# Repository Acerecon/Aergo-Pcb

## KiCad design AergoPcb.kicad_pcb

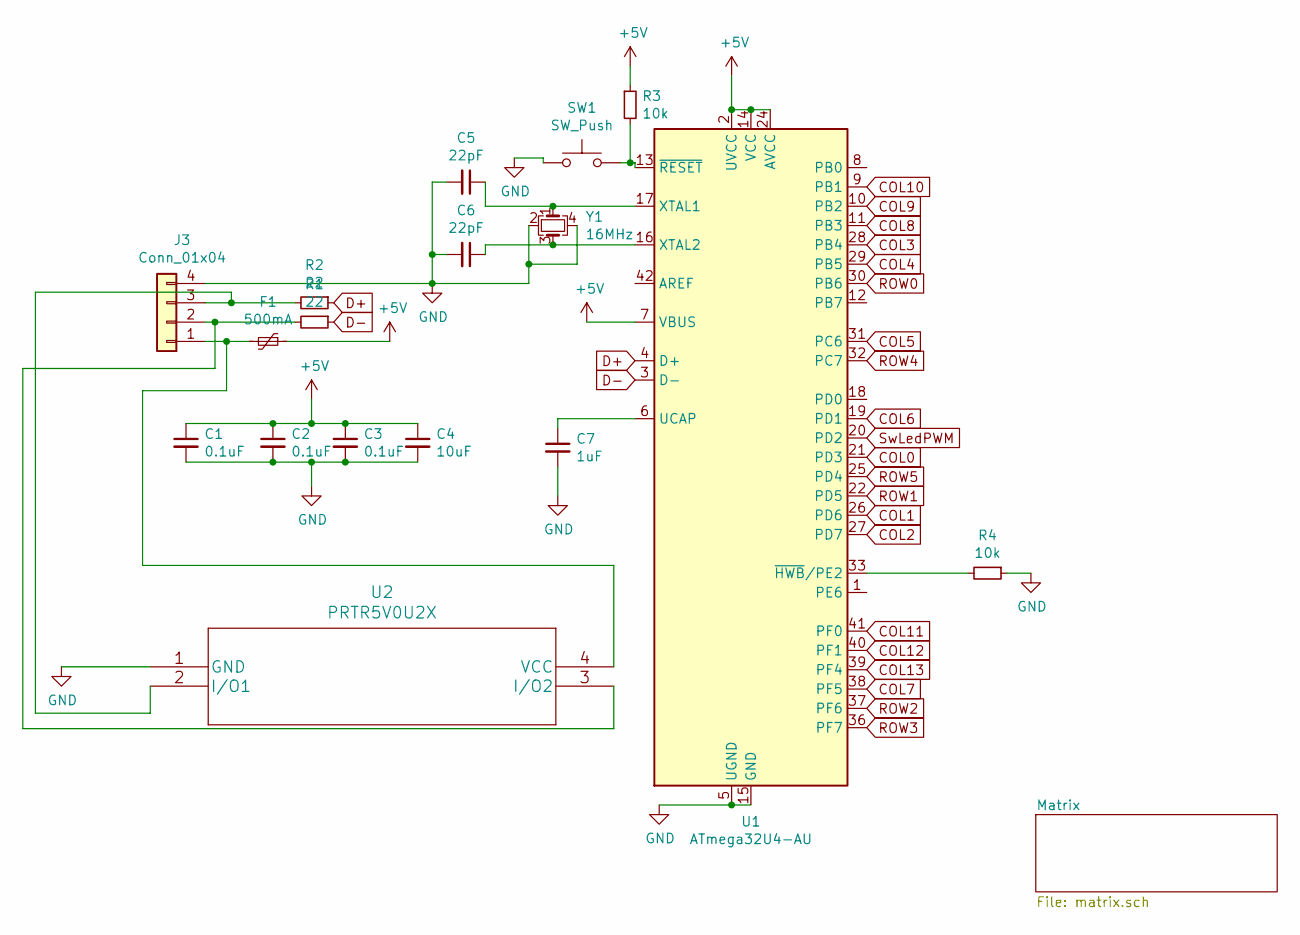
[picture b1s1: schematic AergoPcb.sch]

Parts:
C1, C2, C3: 0.1uF; C_0805_2012Metric
C4: 10uF; C_0805_2012Metric
C5, C6: 22pF; C_0805_2012Metric
C7: 1uF; C_0805_2012Metric
F1: 500mA; Fuse_SMD1206_Reflow
J3: Conn_01x04; JST_SH_SM04B-SRSS-TB_1x04-1MP_P1.00mm_Horizontal
R1, R2: 22; R_0805_2012Metric
R3, R4: 10k; R_0805_2012Metric
SW1: SW_Push; SKQG-1155865
U1: ATmega32U4-AU; TQFP-44_10x10mm_P0.8mm
U2: PRTR5V0U2X; SOT143B
Y1: 16MHz; Crystal_SMD_3225-4Pin_3.2x2.5mm

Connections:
+5V: C1.1, C2.1, C3.1, C4.1, F1.1, R3.1, U1.2 (UVCC), U1.7 (VBUS), U1.14 (VCC), U1.24 (AVCC), U1.34 (VCC), U1.44 (AVCC); also elsewhere on the board
COL0: U1.21 (PD3); also elsewhere on the board
COL1: U1.26 (PD6); also elsewhere on the board
COL2: U1.27 (PD7); also elsewhere on the board
COL3: U1.28 (PB4); also elsewhere on the board
COL4: U1.29 (PB5); also elsewhere on the board
COL5: U1.31 (PC6); also elsewhere on the board
COL6: U1.19 (PD1); also elsewhere on the board
COL7: U1.38 (PF5); also elsewhere on the board
COL8: U1.11 (PB3); also elsewhere on the board
COL9: U1.10 (PB2); also elsewhere on the board
COL10: U1.9 (PB1); also elsewhere on the board
COL11: U1.41 (PF0); also elsewhere on the board
COL12: U1.40 (PF1); also elsewhere on the board
COL13: U1.39 (PF4); also elsewhere on the board
D+: R2.1, U1.4 (D+)
D-: R1.1, U1.3 (D-)
GND: C1.2, C2.2, C3.2, C4.2, C5.2, C6.2, C7.2, J3.4, R4.1, SW1.1, U1.5 (UGND), U1.15 (GND), U1.23 (GND), U1.35 (GND), U1.43 (GND), U2.1 (GND), Y1.2, Y1.4; also elsewhere on the board
unnamed: C5.1, U1.17 (XTAL1), Y1.1
unnamed: C6.1, U1.16 (XTAL2), Y1.3
unnamed: C7.1, U1.6 (UCAP)
unnamed: F1.2, J3.1, U2.4 (VCC)
unnamed: J3.2, R1.2, U2.3 (I/O2)
unnamed: J3.3, R2.2, U2.2 (I/O1)
unnamed: R3.2, SW1.2, U1.13 (~RESET)
unnamed: R4.2, U1.33 (~HWB~/PE2)
ROW0: U1.30 (PB6); also elsewhere on the board
ROW1: U1.22 (PD5); also elsewhere on the board
ROW2: U1.37 (PF6); also elsewhere on the board
ROW3: U1.36 (PF7); also elsewhere on the board
ROW4: U1.32 (PC7); also elsewhere on the board
ROW5: U1.25 (PD4); also elsewhere on the board
SwLedPWM: U1.20 (PD2); also elsewhere on the board

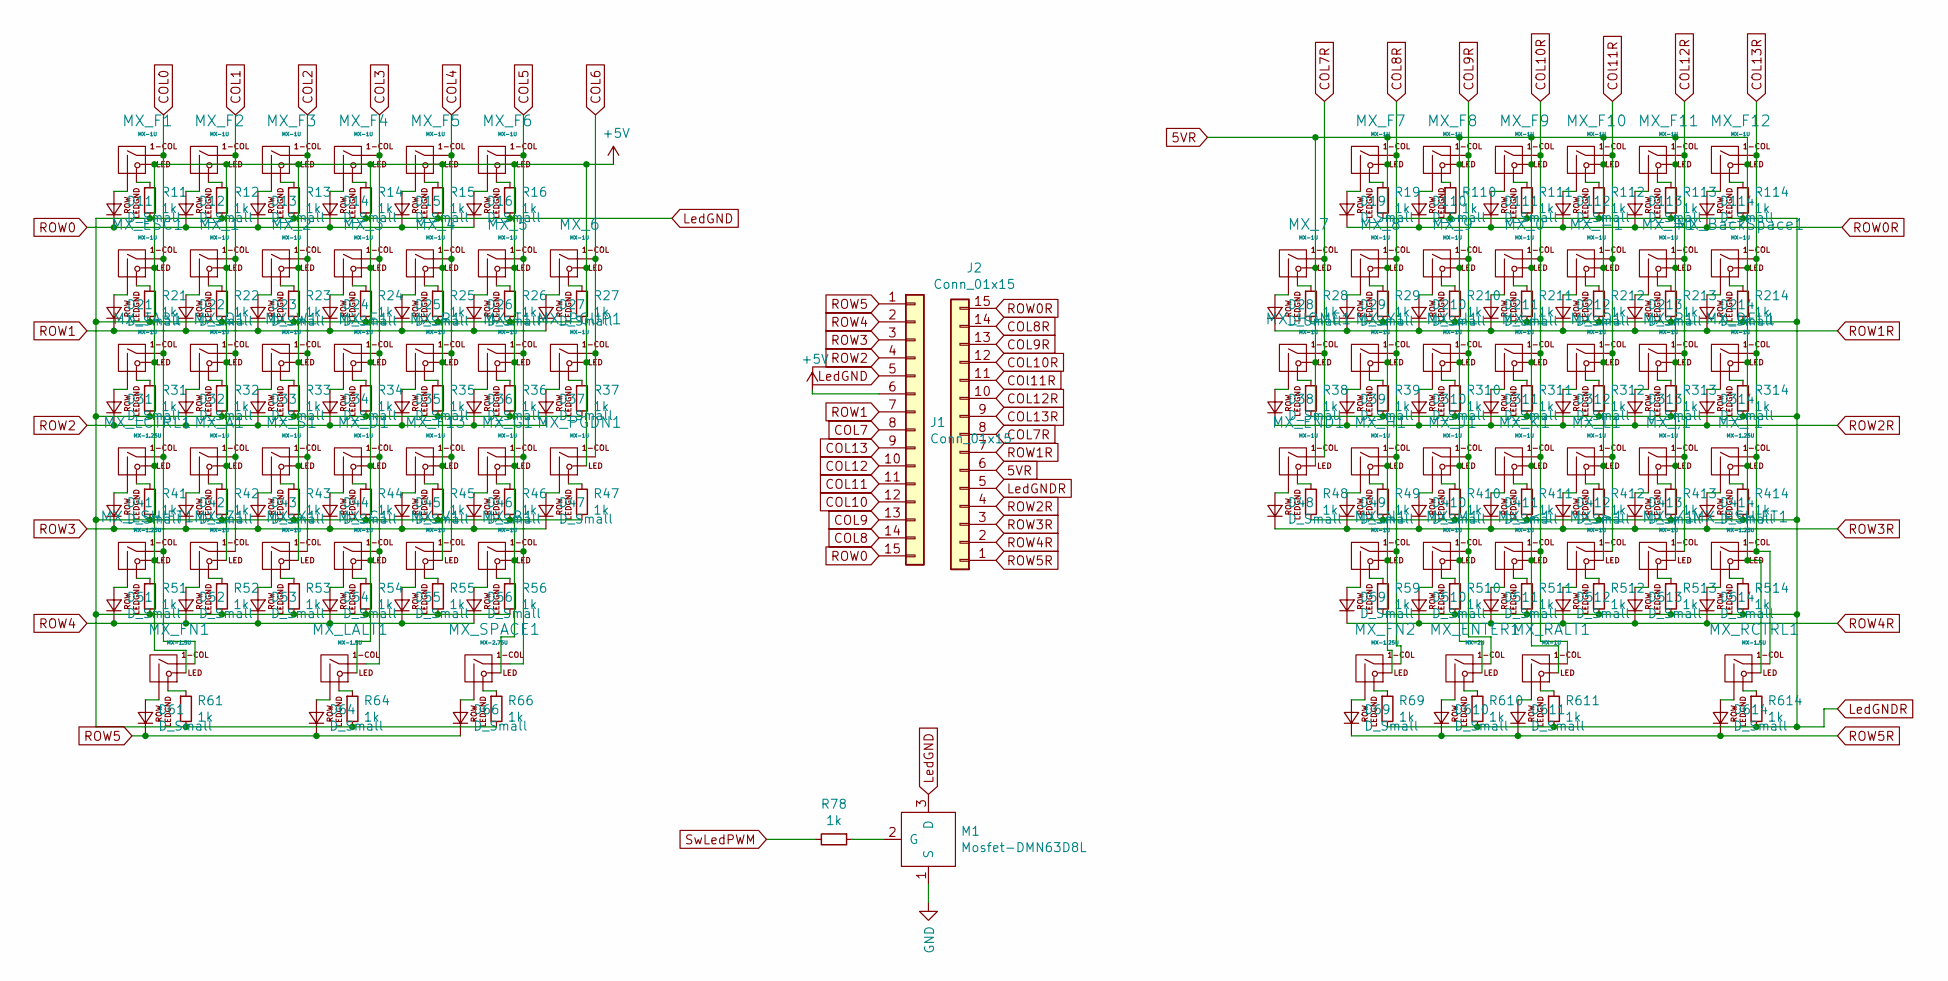
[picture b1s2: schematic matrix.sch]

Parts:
D11, D12, D13, D14, D15, D16, D19, D21, D22, D23, D24, D25, D26, D27, D28, D29, D31, D32, D33, D34, D35, D36, D37, D38, D39, D41, D42, D43, D44, D45, D46, D47, D48, D49, D51, D52, D53, D54, D55, D56, D59, D61, D64, D66, D69, D110, D111, D112, D113, D114, D210, D211, D212, D213, D214, D310, D311, D312, D313, D314, D410, D411, D412, D413, D414, D510, D511, D512, D513, D514, D610, D611, D614: D_Small; D_SOD-123
J1, J2: Conn_01x15; JST_SH_SM15B-SRSS-TB_1x15-1MP_P1.00mm_Horizontal
M1: Mosfet-DMN63D8L
MX_0, MX_1, MX_2, MX_3, MX_4, MX_5, MX_6, MX_7, MX_8, MX_9: MX-1U; MXOnly-1U
MX_'1: MX-1.25U; MXOnly-1.25U
MX_-1: MX-1U; MXOnly-1U
MX_/1: MX-1U; MXOnly-1U
MX_;1: MX-1U; MXOnly-1U
MX_<1: MX-1U; MXOnly-1U
MX_=1: MX-1U; MXOnly-1U
MX_>1: MX-1U; MXOnly-1U
MX_A1: MX-1U; MXOnly-1U
MX_B1: MX-1U; MXOnly-1U
MX_BackSpace1: MX-1U; MXOnly-1U
MX_C1: MX-1U; MXOnly-1U
MX_D1: MX-1U; MXOnly-1U
MX_DEL1: MX-1U; MXOnly-1U
MX_E1: MX-1U; MXOnly-1U
MX_END1: MX-1U; MXOnly-1U
MX_ENTER1: MX-2U; MXOnly-2U-ReversedStabilizers
MX_ESC1: MX-1U; MXOnly-1U
MX_F1, MX_F2, MX_F3, MX_F4, MX_F5, MX_F6, MX_F7, MX_F8, MX_F9, MX_F10, MX_F11, MX_F12, MX_F13: MX-1U; MXOnly-1U
MX_FN1: MX-1.5U; MXOnly-1.5U
MX_FN2: MX-1.25U; MXOnly-1.25U
MX_G1: MX-1U; MXOnly-1U
MX_H1: MX-1U; MXOnly-1U
MX_HOME1: MX-1U; MXOnly-1U
MX_I1: MX-1U; MXOnly-1U
MX_J1: MX-1U; MXOnly-1U
MX_K1: MX-1U; MXOnly-1U
MX_L1: MX-1U; MXOnly-1U
MX_LALT1: MX-1.5U; MXOnly-1.5U
MX_LCTRL1: MX-1.25U; MXOnly-1.25U
MX_LSHIFT1: MX-1.25U; MXOnly-1.25U
MX_M1: MX-1U; MXOnly-1U
MX_N1: MX-1U; MXOnly-1U
MX_O1: MX-1U; MXOnly-1U
MX_P1: MX-1U; MXOnly-1U
MX_PGDN1: MX-1U; MXOnly-1U
MX_PGUP1: MX-1U; MXOnly-1U
MX_Q1: MX-1U; MXOnly-1U
MX_R1: MX-1U; MXOnly-1U
MX_RALT1: MX-1U; MXOnly-1U
MX_RCTRL1: MX-1.5U; MXOnly-1.5U
MX_RSHIFT1: MX-1.25U; MXOnly-1.25U
MX_S1: MX-1U; MXOnly-1U
MX_SPACE1: MX-2.75U; MXOnly-2.75U-ReversedStabilizers
MX_T1: MX-1U; MXOnly-1U
MX_TAB1: MX-1U; MXOnly-1U
MX_U1: MX-1U; MXOnly-1U
MX_V1: MX-1U; MXOnly-1U
MX_W1: MX-1U; MXOnly-1U
MX_X1: MX-1U; MXOnly-1U
MX_Y1: MX-1U; MXOnly-1U
MX_Z1: MX-1U; MXOnly-1U
R11, R12, R13, R14, R15, R16, R19, R21, R22, R23, R24, R25, R26, R27, R28, R29, R31, R32, R33, R34, R35, R36, R37, R38, R39, R41, R42, R43, R44, R45, R46, R47, R48, R49, R51, R52, R53, R54, R55, R56, R59, R61, R64, R66, R69, R78, R110, R111, R112, R113, R114, R210, R211, R212, R213, R214, R310, R311, R312, R313, R314, R410, R411, R412, R413, R414, R510, R511, R512, R513, R514, R610, R611, R614: 1k; R_0805_2012Metric

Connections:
5VR: J2.6, MX_0.3 (LED), MX_7.3 (LED), MX_8.3 (LED), MX_9.3 (LED), MX_'1.3 (LED), MX_-1.3 (LED), MX_/1.3 (LED), MX_;1.3 (LED), MX_<1.3 (LED), MX_=1.3 (LED), MX_>1.3 (LED), MX_BackSpace1.3 (LED), MX_DEL1.3 (LED), MX_END1.3 (LED), MX_ENTER1.3 (LED), MX_F7.3 (LED), MX_F8.3 (LED), MX_F9.3 (LED), MX_F10.3 (LED), MX_F11.3 (LED), MX_F12.3 (LED), MX_FN2.3 (LED), MX_H1.3 (LED), MX_HOME1.3 (LED), MX_I1.3 (LED), MX_J1.3 (LED), MX_K1.3 (LED), MX_L1.3 (LED), MX_M1.3 (LED), MX_N1.3 (LED), MX_O1.3 (LED), MX_P1.3 (LED), MX_RALT1.3 (LED), MX_RCTRL1.3 (LED), MX_RSHIFT1.3 (LED), MX_U1.3 (LED), MX_Y1.3 (LED)
+5V: J1.6, MX_1.3 (LED), MX_2.3 (LED), MX_3.3 (LED), MX_4.3 (LED), MX_5.3 (LED), MX_6.3 (LED), MX_A1.3 (LED), MX_B1.3 (LED), MX_C1.3 (LED), MX_D1.3 (LED), MX_E1.3 (LED), MX_ESC1.3 (LED), MX_F1.3 (LED), MX_F2.3 (LED), MX_F3.3 (LED), MX_F4.3 (LED), MX_F5.3 (LED), MX_F6.3 (LED), MX_F13.3 (LED), MX_FN1.3 (LED), MX_G1.3 (LED), MX_LALT1.3 (LED), MX_LCTRL1.3 (LED), MX_LSHIFT1.3 (LED), MX_PGDN1.3 (LED), MX_PGUP1.3 (LED), MX_Q1.3 (LED), MX_R1.3 (LED), MX_S1.3 (LED), MX_SPACE1.3 (LED), MX_T1.3 (LED), MX_TAB1.3 (LED), MX_V1.3 (LED), MX_W1.3 (LED), MX_X1.3 (LED), MX_Z1.3 (LED); also elsewhere on the board
COL0: MX_ESC1.1 (COL), MX_F1.1 (COL), MX_FN1.1 (COL), MX_LCTRL1.1 (COL), MX_LSHIFT1.1 (COL), MX_TAB1.1 (COL); also elsewhere on the board
COL1: MX_1.1 (COL), MX_A1.1 (COL), MX_F2.1 (COL), MX_Q1.1 (COL), MX_Z1.1 (COL); also elsewhere on the board
COL2: MX_2.1 (COL), MX_F3.1 (COL), MX_S1.1 (COL), MX_W1.1 (COL), MX_X1.1 (COL); also elsewhere on the board
COL3: MX_3.1 (COL), MX_C1.1 (COL), MX_D1.1 (COL), MX_E1.1 (COL), MX_F4.1 (COL), MX_LALT1.1 (COL); also elsewhere on the board
COL4: MX_4.1 (COL), MX_F5.1 (COL), MX_F13.1 (COL), MX_R1.1 (COL), MX_V1.1 (COL); also elsewhere on the board
COL5: MX_5.1 (COL), MX_B1.1 (COL), MX_F6.1 (COL), MX_G1.1 (COL), MX_SPACE1.1 (COL), MX_T1.1 (COL); also elsewhere on the board
COL6: MX_6.1 (COL), MX_PGDN1.1 (COL), MX_PGUP1.1 (COL); also elsewhere on the board
COL7: J1.8; also elsewhere on the board
COL7R: J2.8, MX_7.1 (COL), MX_END1.1 (COL), MX_HOME1.1 (COL)
COL8: J1.14; also elsewhere on the board
COL8R: J2.14, MX_8.1 (COL), MX_F7.1 (COL), MX_FN2.1 (COL), MX_H1.1 (COL), MX_N1.1 (COL), MX_Y1.1 (COL)
COL9: J1.13; also elsewhere on the board
COL9R: J2.13, MX_9.1 (COL), MX_ENTER1.1 (COL), MX_F8.1 (COL), MX_J1.1 (COL), MX_M1.1 (COL), MX_U1.1 (COL)
COL10: J1.12; also elsewhere on the board
COL10R: J2.12, MX_0.1 (COL), MX_<1.1 (COL), MX_F9.1 (COL), MX_I1.1 (COL), MX_K1.1 (COL), MX_RALT1.1 (COL)
COL11: J1.11; also elsewhere on the board
COL12: J1.10; also elsewhere on the board
COL12R: J2.10, MX_/1.1 (COL), MX_;1.1 (COL), MX_=1.1 (COL), MX_F11.1 (COL), MX_P1.1 (COL)
COL13: J1.9; also elsewhere on the board
COL13R: J2.9, MX_'1.1 (COL), MX_BackSpace1.1 (COL), MX_DEL1.1 (COL), MX_F12.1 (COL), MX_RCTRL1.1 (COL), MX_RSHIFT1.1 (COL)
COl11R: J2.11, MX_-1.1 (COL), MX_>1.1 (COL), MX_F10.1 (COL), MX_L1.1 (COL), MX_O1.1 (COL)
GND: M1.1 (S); also elsewhere on the board
LedGND: J1.5, M1.3 (D), R11.2, R12.2, R13.2, R14.2, R15.2, R16.2, R21.2, R22.2, R23.2, R24.2, R25.2, R26.2, R27.2, R31.2, R32.2, R33.2, R34.2, R35.2, R36.2, R37.2, R41.2, R42.2, R43.2, R44.2, R45.2, R46.2, R47.2, R51.2, R52.2, R53.2, R54.2, R55.2, R56.2, R61.2, R64.2, R66.2
LedGNDR: J2.5, R19.2, R28.2, R29.2, R38.2, R39.2, R48.2, R49.2, R59.2, R69.2, R110.2, R111.2, R112.2, R113.2, R114.2, R210.2, R211.2, R212.2, R213.2, R214.2, R310.2, R311.2, R312.2, R313.2, R314.2, R410.2, R411.2, R412.2, R413.2, R414.2, R510.2, R511.2, R512.2, R513.2, R514.2, R610.2, R611.2, R614.2
unnamed: D11.2 (A), MX_F1.2 (ROW)
unnamed: D12.2 (A), MX_F2.2 (ROW)
unnamed: D13.2 (A), MX_F3.2 (ROW)
unnamed: D14.2 (A), MX_F4.2 (ROW)
unnamed: D15.2 (A), MX_F5.2 (ROW)
unnamed: D16.2 (A), MX_F6.2 (ROW)
unnamed: D19.2 (A), MX_F7.2 (ROW)
unnamed: D21.2 (A), MX_ESC1.2 (ROW)
unnamed: D22.2 (A), MX_1.2 (ROW)
unnamed: D23.2 (A), MX_2.2 (ROW)
unnamed: D24.2 (A), MX_3.2 (ROW)
unnamed: D25.2 (A), MX_4.2 (ROW)
unnamed: D26.2 (A), MX_5.2 (ROW)
unnamed: D27.2 (A), MX_6.2 (ROW)
unnamed: D28.2 (A), MX_7.2 (ROW)
unnamed: D29.2 (A), MX_8.2 (ROW)
unnamed: D31.2 (A), MX_TAB1.2 (ROW)
unnamed: D32.2 (A), MX_Q1.2 (ROW)
unnamed: D33.2 (A), MX_W1.2 (ROW)
unnamed: D34.2 (A), MX_E1.2 (ROW)
unnamed: D35.2 (A), MX_R1.2 (ROW)
unnamed: D36.2 (A), MX_T1.2 (ROW)
unnamed: D37.2 (A), MX_PGUP1.2 (ROW)
unnamed: D38.2 (A), MX_HOME1.2 (ROW)
unnamed: D39.2 (A), MX_Y1.2 (ROW)
unnamed: D41.2 (A), MX_LCTRL1.2 (ROW)
unnamed: D42.2 (A), MX_A1.2 (ROW)
unnamed: D43.2 (A), MX_S1.2 (ROW)
unnamed: D44.2 (A), MX_D1.2 (ROW)
unnamed: D45.2 (A), MX_F13.2 (ROW)
unnamed: D46.2 (A), MX_G1.2 (ROW)
unnamed: D47.2 (A), MX_PGDN1.2 (ROW)
unnamed: D48.2 (A), MX_END1.2 (ROW)
unnamed: D49.2 (A), MX_H1.2 (ROW)
unnamed: D51.2 (A), MX_LSHIFT1.2 (ROW)
unnamed: D52.2 (A), MX_Z1.2 (ROW)
unnamed: D53.2 (A), MX_X1.2 (ROW)
unnamed: D54.2 (A), MX_C1.2 (ROW)
unnamed: D55.2 (A), MX_V1.2 (ROW)
unnamed: D56.2 (A), MX_B1.2 (ROW)
unnamed: D59.2 (A), MX_N1.2 (ROW)
unnamed: D61.2 (A), MX_FN1.2 (ROW)
unnamed: D64.2 (A), MX_LALT1.2 (ROW)
unnamed: D66.2 (A), MX_SPACE1.2 (ROW)
unnamed: D69.2 (A), MX_FN2.2 (ROW)
unnamed: D110.2 (A), MX_F8.2 (ROW)
unnamed: D111.2 (A), MX_F9.2 (ROW)
unnamed: D112.2 (A), MX_F10.2 (ROW)
unnamed: D113.2 (A), MX_F11.2 (ROW)
unnamed: D114.2 (A), MX_F12.2 (ROW)
unnamed: D210.2 (A), MX_9.2 (ROW)
unnamed: D211.2 (A), MX_0.2 (ROW)
unnamed: D212.2 (A), MX_-1.2 (ROW)
unnamed: D213.2 (A), MX_=1.2 (ROW)
unnamed: D214.2 (A), MX_BackSpace1.2 (ROW)
unnamed: D310.2 (A), MX_U1.2 (ROW)
unnamed: D311.2 (A), MX_I1.2 (ROW)
unnamed: D312.2 (A), MX_O1.2 (ROW)
unnamed: D313.2 (A), MX_P1.2 (ROW)
unnamed: D314.2 (A), MX_DEL1.2 (ROW)
unnamed: D410.2 (A), MX_J1.2 (ROW)
unnamed: D411.2 (A), MX_K1.2 (ROW)
unnamed: D412.2 (A), MX_L1.2 (ROW)
unnamed: D413.2 (A), MX_;1.2 (ROW)
unnamed: D414.2 (A), MX_'1.2 (ROW)
unnamed: D510.2 (A), MX_M1.2 (ROW)
unnamed: D511.2 (A), MX_<1.2 (ROW)
unnamed: D512.2 (A), MX_>1.2 (ROW)
unnamed: D513.2 (A), MX_/1.2 (ROW)
unnamed: D514.2 (A), MX_RSHIFT1.2 (ROW)
unnamed: D610.2 (A), MX_ENTER1.2 (ROW)
unnamed: D611.2 (A), MX_RALT1.2 (ROW)
unnamed: D614.2 (A), MX_RCTRL1.2 (ROW)
unnamed: M1.2 (G), R78.1
unnamed: MX_0.4 (LEDGND), R211.1
unnamed: MX_1.4 (LEDGND), R22.1
unnamed: MX_2.4 (LEDGND), R23.1
unnamed: MX_3.4 (LEDGND), R24.1
unnamed: MX_4.4 (LEDGND), R25.1
unnamed: MX_5.4 (LEDGND), R26.1
unnamed: MX_6.4 (LEDGND), R27.1
unnamed: MX_7.4 (LEDGND), R28.1
unnamed: MX_8.4 (LEDGND), R29.1
unnamed: MX_9.4 (LEDGND), R210.1
unnamed: MX_'1.4 (LEDGND), R414.1
unnamed: MX_-1.4 (LEDGND), R212.1
unnamed: MX_/1.4 (LEDGND), R513.1
unnamed: MX_;1.4 (LEDGND), R413.1
unnamed: MX_<1.4 (LEDGND), R511.1
unnamed: MX_=1.4 (LEDGND), R213.1
unnamed: MX_>1.4 (LEDGND), R512.1
unnamed: MX_A1.4 (LEDGND), R42.1
unnamed: MX_B1.4 (LEDGND), R56.1
unnamed: MX_BackSpace1.4 (LEDGND), R214.1
unnamed: MX_C1.4 (LEDGND), R54.1
unnamed: MX_D1.4 (LEDGND), R44.1
unnamed: MX_DEL1.4 (LEDGND), R314.1
unnamed: MX_E1.4 (LEDGND), R34.1
unnamed: MX_END1.4 (LEDGND), R48.1
unnamed: MX_ENTER1.4 (LEDGND), R610.1
unnamed: MX_ESC1.4 (LEDGND), R21.1
unnamed: MX_F1.4 (LEDGND), R11.1
unnamed: MX_F2.4 (LEDGND), R12.1
unnamed: MX_F3.4 (LEDGND), R13.1
unnamed: MX_F4.4 (LEDGND), R14.1
unnamed: MX_F5.4 (LEDGND), R15.1
unnamed: MX_F6.4 (LEDGND), R16.1
unnamed: MX_F7.4 (LEDGND), R19.1
unnamed: MX_F8.4 (LEDGND), R110.1
unnamed: MX_F9.4 (LEDGND), R111.1
unnamed: MX_F10.4 (LEDGND), R112.1
unnamed: MX_F11.4 (LEDGND), R113.1
unnamed: MX_F12.4 (LEDGND), R114.1
unnamed: MX_F13.4 (LEDGND), R45.1
unnamed: MX_FN1.4 (LEDGND), R61.1
unnamed: MX_FN2.4 (LEDGND), R69.1
unnamed: MX_G1.4 (LEDGND), R46.1
unnamed: MX_H1.4 (LEDGND), R49.1
unnamed: MX_HOME1.4 (LEDGND), R38.1
unnamed: MX_I1.4 (LEDGND), R311.1
unnamed: MX_J1.4 (LEDGND), R410.1
unnamed: MX_K1.4 (LEDGND), R411.1
unnamed: MX_L1.4 (LEDGND), R412.1
unnamed: MX_LALT1.4 (LEDGND), R64.1
unnamed: MX_LCTRL1.4 (LEDGND), R41.1
unnamed: MX_LSHIFT1.4 (LEDGND), R51.1
unnamed: MX_M1.4 (LEDGND), R510.1
unnamed: MX_N1.4 (LEDGND), R59.1
unnamed: MX_O1.4 (LEDGND), R312.1
unnamed: MX_P1.4 (LEDGND), R313.1
unnamed: MX_PGDN1.4 (LEDGND), R47.1
unnamed: MX_PGUP1.4 (LEDGND), R37.1
unnamed: MX_Q1.4 (LEDGND), R32.1
unnamed: MX_R1.4 (LEDGND), R35.1
unnamed: MX_RALT1.4 (LEDGND), R611.1
unnamed: MX_RCTRL1.4 (LEDGND), R614.1
unnamed: MX_RSHIFT1.4 (LEDGND), R514.1
unnamed: MX_S1.4 (LEDGND), R43.1
unnamed: MX_SPACE1.4 (LEDGND), R66.1
unnamed: MX_T1.4 (LEDGND), R36.1
unnamed: MX_TAB1.4 (LEDGND), R31.1
unnamed: MX_U1.4 (LEDGND), R310.1
unnamed: MX_V1.4 (LEDGND), R55.1
unnamed: MX_W1.4 (LEDGND), R33.1
unnamed: MX_X1.4 (LEDGND), R53.1
unnamed: MX_Y1.4 (LEDGND), R39.1
unnamed: MX_Z1.4 (LEDGND), R52.1
ROW0: D11.1 (K), D12.1 (K), D13.1 (K), D14.1 (K), D15.1 (K), D16.1 (K), J1.15; also elsewhere on the board
ROW0R: D19.1 (K), D110.1 (K), D111.1 (K), D112.1 (K), D113.1 (K), D114.1 (K), J2.15
ROW1: D21.1 (K), D22.1 (K), D23.1 (K), D24.1 (K), D25.1 (K), D26.1 (K), D27.1 (K), J1.7; also elsewhere on the board
ROW1R: D28.1 (K), D29.1 (K), D210.1 (K), D211.1 (K), D212.1 (K), D213.1 (K), D214.1 (K), J2.7
ROW2: D31.1 (K), D32.1 (K), D33.1 (K), D34.1 (K), D35.1 (K), D36.1 (K), D37.1 (K), J1.4; also elsewhere on the board
ROW2R: D38.1 (K), D39.1 (K), D310.1 (K), D311.1 (K), D312.1 (K), D313.1 (K), D314.1 (K), J2.4
ROW3: D41.1 (K), D42.1 (K), D43.1 (K), D44.1 (K), D45.1 (K), D46.1 (K), D47.1 (K), J1.3; also elsewhere on the board
ROW3R: D48.1 (K), D49.1 (K), D410.1 (K), D411.1 (K), D412.1 (K), D413.1 (K), D414.1 (K), J2.3
ROW4: D51.1 (K), D52.1 (K), D53.1 (K), D54.1 (K), D55.1 (K), D56.1 (K), J1.2; also elsewhere on the board
ROW4R: D59.1 (K), D510.1 (K), D511.1 (K), D512.1 (K), D513.1 (K), D514.1 (K), J2.2
ROW5: D61.1 (K), D64.1 (K), D66.1 (K), J1.1; also elsewhere on the board
ROW5R: D69.1 (K), D610.1 (K), D611.1 (K), D614.1 (K), J2.1
SwLedPWM: R78.2; also elsewhere on the board

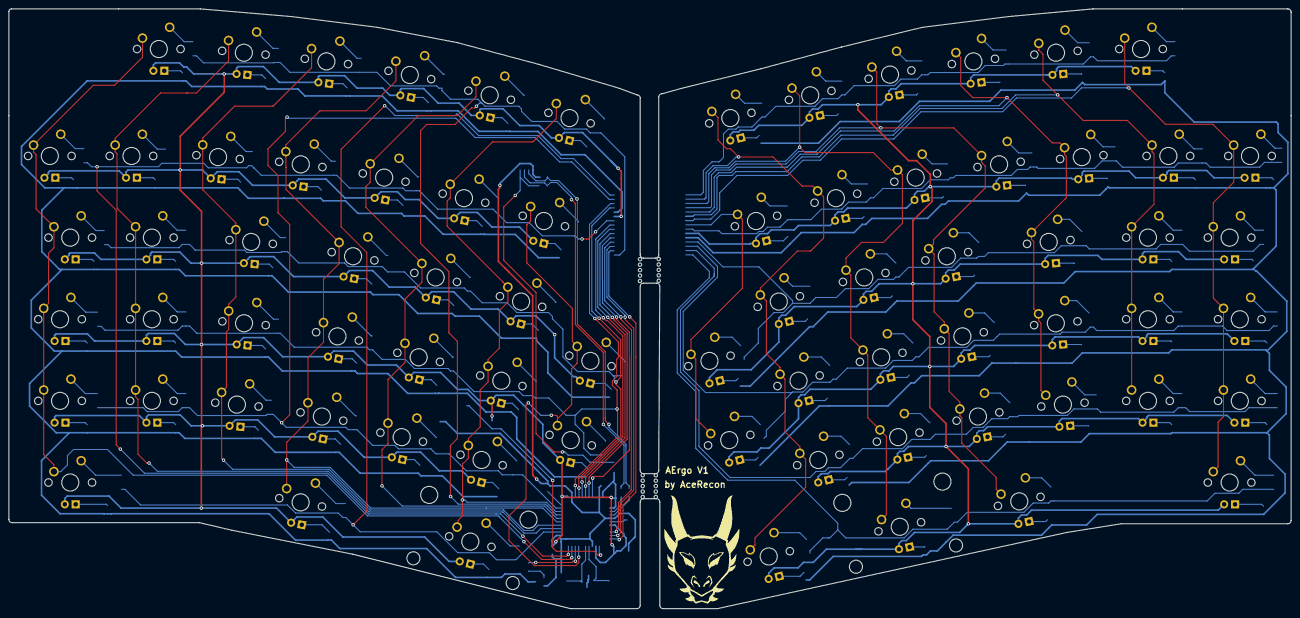
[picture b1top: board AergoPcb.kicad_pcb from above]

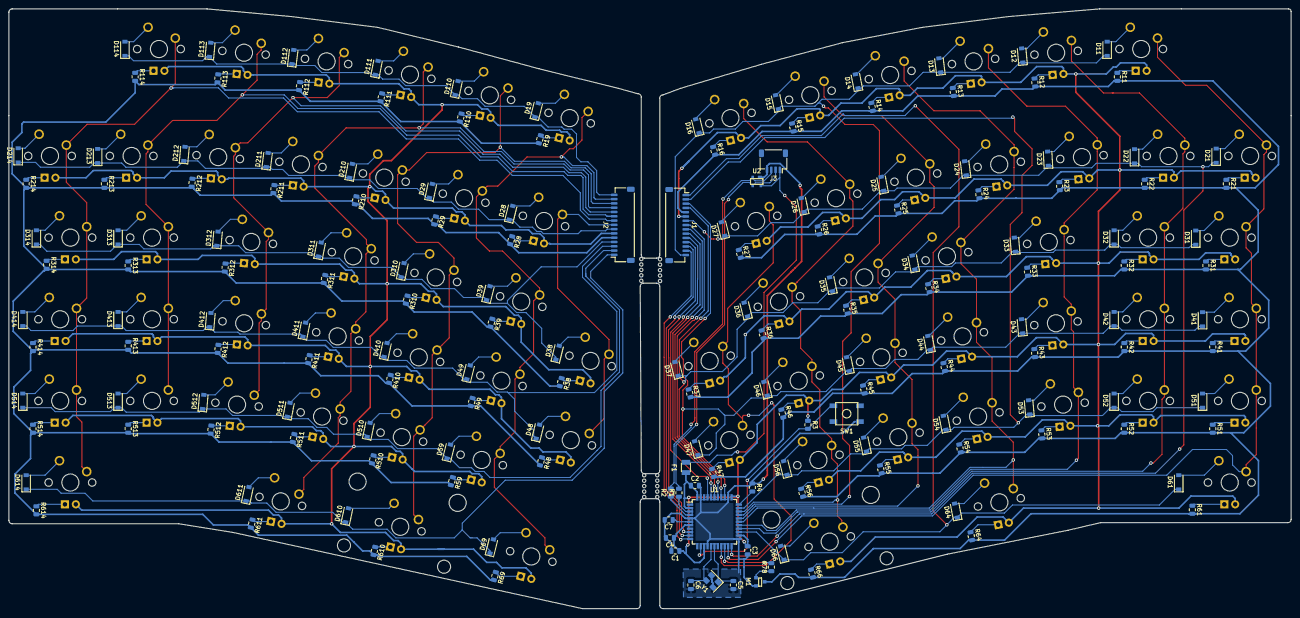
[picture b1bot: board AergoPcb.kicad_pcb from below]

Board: 2 copper layers, 299.2 x 140.0 mm, 240 parts (167 on the bottom side), 196 nets.

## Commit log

2019-03-07 Initialized project and created PCB schematics
2019-03-07 Add submodules
2019-03-07 added libraries
2019-03-11 added libaries
2019-03-22 more work, added rgb strip and backlighting
2019-03-22 brought in daughterboard
2019-03-22 added type c
2019-03-27 added jst footprints, continued work on pcb
2019-03-31 finished right half, loaded keyboard parts pretty
2019-04-07 Finalized PCB and created Gerbers
2019-04-24 remade gerbers
2019-05-04 more pcb work
